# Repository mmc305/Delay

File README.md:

# Delay-Pedal

use PT2399 IC

three vaariables: Level, Time, Repeats

references:
- https://www.youtube.com/watch?v=N7Y_1qoq_eM
- https://www.diyguitarpedals.com.au/shop/index.php?main_page=product_info&cPath=35&products_id=633

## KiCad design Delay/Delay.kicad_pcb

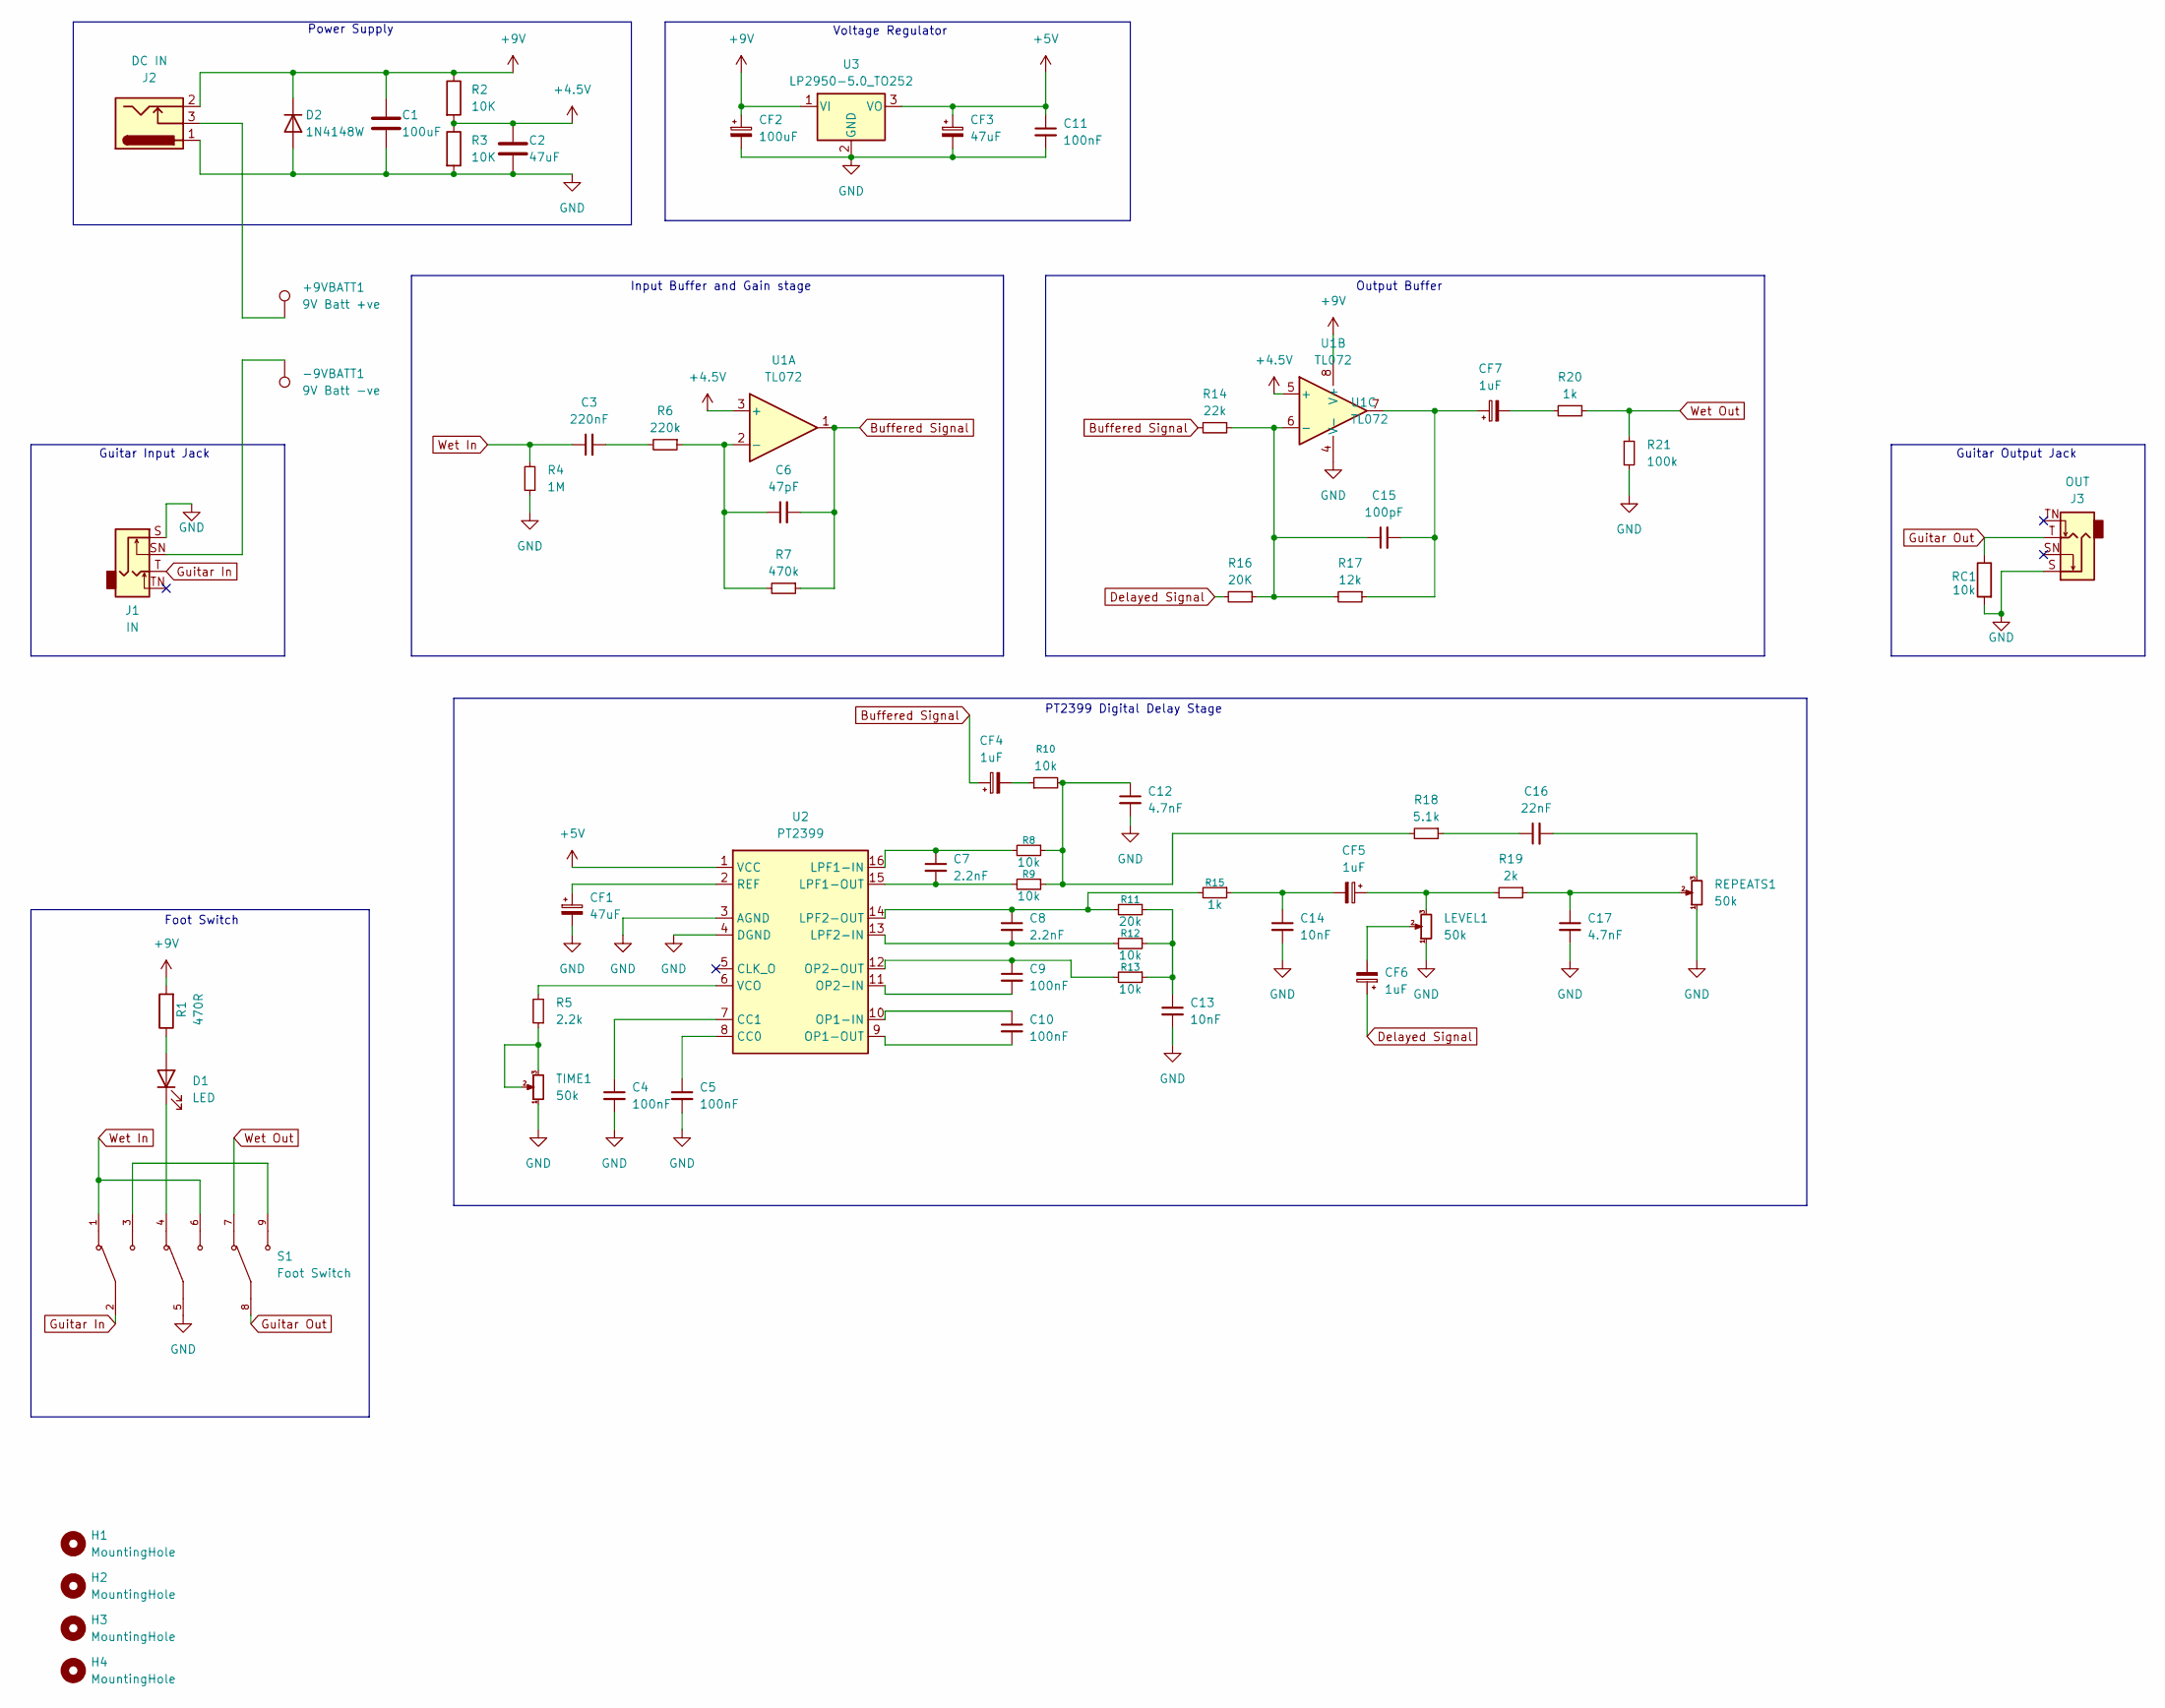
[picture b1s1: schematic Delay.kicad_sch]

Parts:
+9VBATT1: 9V Batt +ve; TestPoint_THTPad_2.5x2.5mm_Drill1.2mm
-9VBATT1: 9V Batt -ve; TestPoint_THTPad_2.5x2.5mm_Drill1.2mm
C1: 100uF; C_1206_3216Metric
C2: 47uF; C_1206_3216Metric
C3: 220nF; C_0603_1608Metric
C4, C5, C9, C10, C11: 100nF; C_0603_1608Metric
C6: 47pF; C_0603_1608Metric
C7, C8: 2.2nF; C_0603_1608Metric
C12, C17: 4.7nF; C_0603_1608Metric
C13, C14: 10nF; C_0603_1608Metric
C15: 100pF; C_0603_1608Metric
C16: 22nF; C_0603_1608Metric
CF1, CF3: 47uF; CP_Radial_D6.3mm_P2.50mm
CF2: 100uF; CP_Radial_D6.3mm_P2.50mm
CF4, CF5, CF6, CF7: 1uF; CP_Radial_D5.0mm_P2.50mm
D1: LED; LED_D3.0mm_Clear
D2: 1N4148W; D_SOD-123
H1, H2, H3, H4: MountingHole; MountingHole_3.2mm_M3_Pad_Via
J1: IN; Jack_6.35mm_Neutrik_NMJ6HFD2_Horizontal
J2: DC IN; BarrelJack_GCT_DCJ200-10-A_Horizontal
J3: OUT; Jack_6.35mm_Neutrik_NMJ6HFD2_Horizontal
LEVEL1: 50k; Potentiometer_RK097_Single_Vertical
R1: 470R; R_0603_1608Metric
R2, R3: 10K; R_0603_1608Metric
R4: 1M; R_0603_1608Metric
R5: 2.2k; R_0603_1608Metric
R6: 220k; R_0603_1608Metric
R7: 470k; R_0603_1608Metric
R8, R9, R10, R12, R13: 10k; R_0603_1608Metric
R11: 20k; R_0603_1608Metric
R14: 22k; R_0603_1608Metric
R15, R20: 1k; R_0603_1608Metric
R16: 20K; R_0603_1608Metric
R17: 12k; R_0603_1608Metric
R18: 5.1k; R_0603_1608Metric
R19: 2k; R_0603_1608Metric
R21: 100k; R_0603_1608Metric
RC1: 10k; R_0603_1608Metric
REPEATS1: 50k; Potentiometer_RK097_Single_Vertical
S1: Foot Switch; 3PDT Foot Switch
TIME1: 50k; Potentiometer_RK097_Single_Vertical
U1: TL072; SOIC-8_5.3x6.2mm_P1.27mm
U2: PT2399; SO-16_3.9x9.9mm_P1.27mm
U3: LP2950-5.0_TO252; TO-252-2

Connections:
+4.5V: C2.1, R2.2, R3.1, U1.3 (+), U1.5 (+)
+5V: C11.1, CF3.1, U2.1 (VCC), U3.3 (VO)
+9V: C1.1, CF2.1, D2.1 (K), J2.2, R1.2, R2.1, U1.8 (V+), U3.1 (VI)
Buffered Signal: C6.2, CF4.1, R7.1, R14.2, U1.1
Delayed Signal: CF6.1, R16.2
GND: C1.2, C2.2, C4.2, C5.2, C11.2, C12.2, C13.2, C14.2, C17.2, CF1.2, CF2.2, CF3.2, D2.2 (A), J1.S, J2.1, J3.S, LEVEL1.1, R3.2, R4.1, R21.2, RC1.2, REPEATS1.1, S1.5, TIME1.1, U1.4 (V-), U2.3 (AGND), U2.4 (DGND), U3.2 (GND)
Guitar In: J1.T, S1.2
Guitar Out: J3.T, RC1.1, S1.8
unnamed: +9VBATT1.1, J2.3
unnamed: -9VBATT1.1, J1.SN
unnamed: C3.2, R6.2
unnamed: C12.1, R8.1, R9.1, R10.2, R18.2
unnamed: C13.1, R11.1, R12.1, R13.1
unnamed: C14.1, CF5.2, R15.1
unnamed: C15.2, CF7.1, R17.1, U1.7
unnamed: C16.1, R18.1
unnamed: C16.2, REPEATS1.3
unnamed: C17.1, R19.1, REPEATS1.2
unnamed: CF4.2, R10.1
unnamed: CF5.1, LEVEL1.3, R19.2
unnamed: CF6.2, LEVEL1.2
unnamed: CF7.2, R20.2
unnamed: D1.2 (A), R1.1
unnamed: D1.1 (K), S1.4
unnamed: R5.1, TIME1.2, TIME1.3
unnamed: S1.3, S1.9
unnamed: C6.1, R6.1, R7.2, U1.2 (-)
unnamed: C15.1, R14.1, R16.1, R17.2, U1.6 (-)
unnamed: C5.1, U2.8 (CC0)
unnamed: C4.1, U2.7 (CC1)
unnamed: C7.1, R8.2, U2.16 (LPF1-IN)
unnamed: C7.2, R9.2, U2.15 (LPF1-OUT)
unnamed: C8.2, R12.2, U2.13 (LPF2-IN)
unnamed: C8.1, R11.2, R15.2, U2.14 (LPF2-OUT)
unnamed: C10.1, U2.10 (OP1-IN)
unnamed: C10.2, U2.9 (OP1-OUT)
unnamed: C9.2, U2.11 (OP2-IN)
unnamed: C9.1, R13.2, U2.12 (OP2-OUT)
unnamed: CF1.1, U2.2 (REF)
unnamed: R5.2, U2.6 (VCO)
Wet In: C3.1, R4.2, S1.1, S1.6
Wet Out: R20.1, R21.1, S1.7

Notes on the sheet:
Guitar Output Jack
Voltage Regulator
Guitar Input Jack
Foot Switch
Power Supply
Output Buffer
Input Buffer and Gain stage
PT2399 Digital Delay Stage

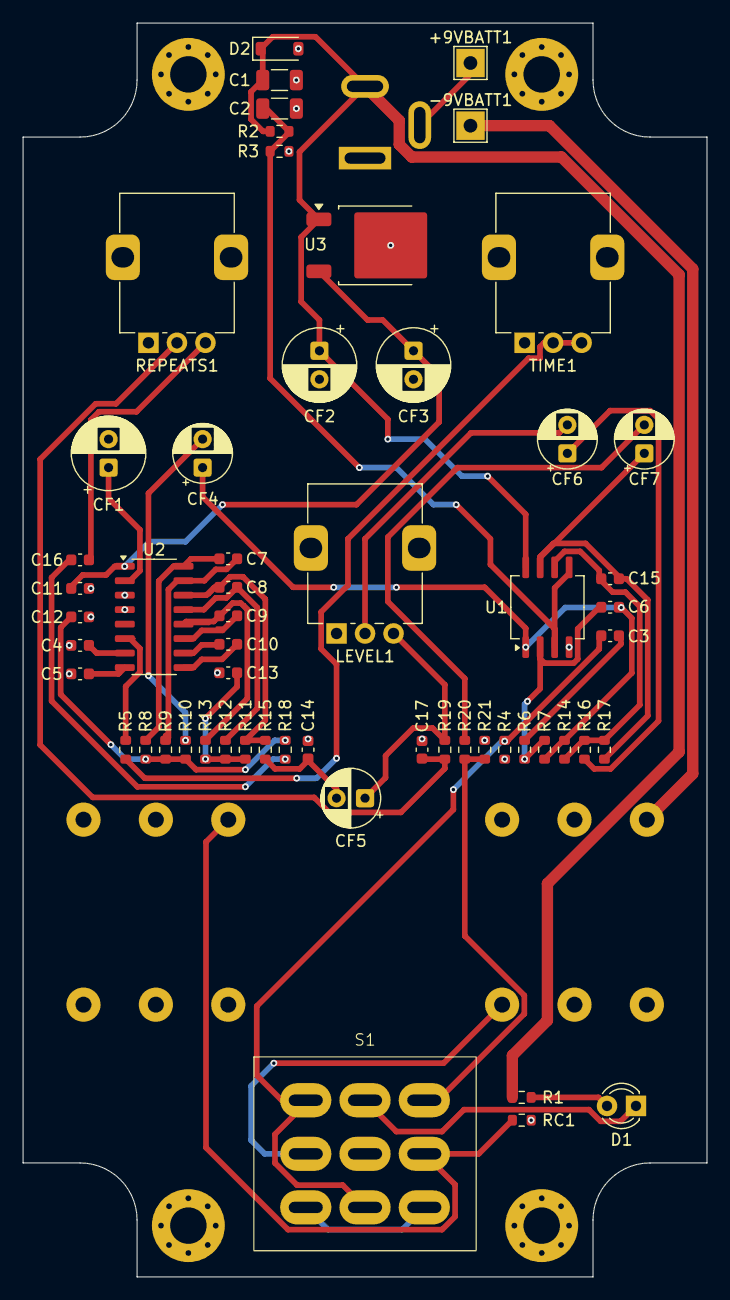
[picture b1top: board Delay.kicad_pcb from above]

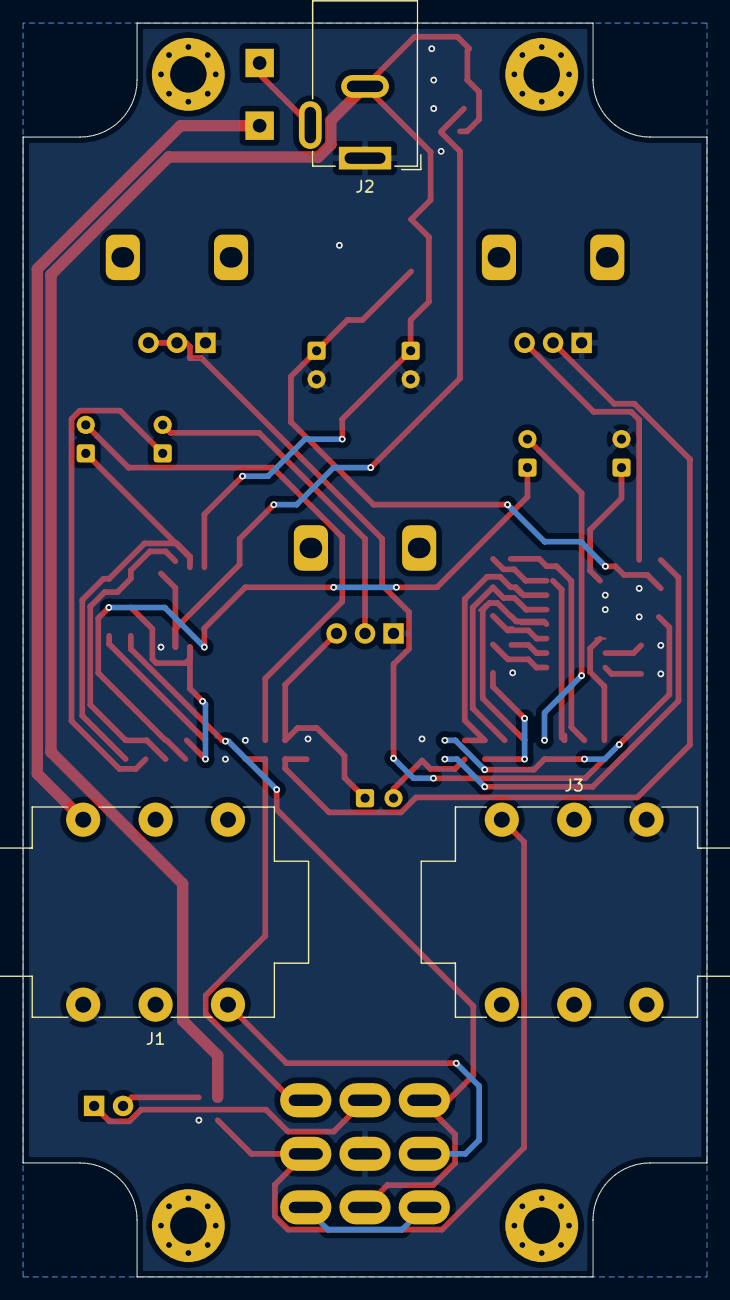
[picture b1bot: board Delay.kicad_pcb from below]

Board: 2 copper layers, 60.0 x 110.0 mm, 64 parts (3 on the bottom side), 42 nets.

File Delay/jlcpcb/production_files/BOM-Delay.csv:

Comment,Designator,Footprint,LCSC,Quantity
PT2399,U2,SO-16_3.9x9.9mm_P1.27mm,C126407,1
100nF,"C10,C11,C4,C5,C9",C_0603_1608Metric,C14663,5
100pF,C15,C_0603_1608Metric,C14858,1
100uF,C1,C_1206_3216Metric,C15008,1
2.2nF,"C7,C8",C_0603_1608Metric,C1604,2
47pF,C6,C_0603_1608Metric,C1671,1
220nF,C3,C_0603_1608Metric,C21120,1
22nF,C16,C_0603_1608Metric,C21122,1
1k,"R15,R20",R_0603_1608Metric,C21190,2
12k,R17,R_0603_1608Metric,C22790,1
1M,R4,R_0603_1608Metric,C22935,1
220k,R6,R_0603_1608Metric,C22961,1
2k,R19,R_0603_1608Metric,C22975,1
470k,R7,R_0603_1608Metric,C23178,1
470R,R1,R_0603_1608Metric,C23179,1
5.1k,R18,R_0603_1608Metric,C23186,1
100k,R21,R_0603_1608Metric,C25803,1
10k,"R10,R12,R13,R2,R3,R8,R9,RC1",R_0603_1608Metric,C25804,8
22k,R14,R_0603_1608Metric,C31850,1
20k,"R11,R16",R_0603_1608Metric,C4184,2
2.2k,R5,R_0603_1608Metric,C4190,1
4.7nF,"C12,C17",C_0603_1608Metric,C53987,2
10nF,"C13,C14",C_0603_1608Metric,C57112,2
LP2950-5.0_TO252,U3,TO-252-2,C68189,1
TL072,U1,SOIC-8_5.3x6.2mm_P1.27mm,C6961,1
1N4148W,D2,D_SOD-123,C81598,1
47uF,C2,C_1206_3216Metric,C96123,1

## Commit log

2025-06-29 made KiCad Project
2025-06-29 Schematic Complete. Need to finalise footprints and PCB layout.
2025-07-02 Completed PCB layout, still need to finish BOM.
2025-07-03 Finalised PCB layout (110mmx60mm) and completed BOM (apart from C1 is only rated for 6.3V which might need to change).
2025-07-03 moved input jack to match the x height of the output jack (it was off by 0.5mm)
2025-07-24 changed caps to be THT and to be sourced separately.
